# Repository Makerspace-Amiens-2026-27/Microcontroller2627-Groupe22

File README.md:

# Nom du projet

> [!IMPORTANT]
> **À modifier** : ce repo a été créé depuis le template de projet du MakerSpace d'Amiens.
> Remplacez ce README par la présentation de votre projet.
> Les guides d'utilisation du template sont sur le
> [site de documentation du MakerSpace](https://doc.makerspace-amiens.fr/workshops/methodologie-de-projet/).

Une phrase qui explique ce que fait le projet et pour qui.

- **Documentation :** [site du projet](https://makerspace-amiens.github.io/template-project/) (sources dans [`docs/`](docs/))
- **Fichiers du projet :** [`project/`](project/) (CAO, électronique, code)

## Équipe 22

- Maxence DUHAMEL
- Romain DELLIEUX

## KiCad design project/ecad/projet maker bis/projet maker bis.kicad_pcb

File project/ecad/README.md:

# Conception électronique

Un dossier par projet KiCad, contenant au minimum les fichiers `.kicad_pro`,
`.kicad_sch` et `.kicad_pcb`.

| Carte | Dossier | Rôle |
|---|---|---|
| Carte principale, rev A (2 couches) | `projet maker/` | XIAO ESP32S3, écran TFT, joystick, 2 boutons, LED, connecteur I2C |
| Carte principale, rev B (1 couche) | `projet maker bis/` | Même schéma, routage sur une seule face, dessous = plan de masse, 0 via |

Le projet a été fait avec **KiCad 10**. Les bibliothèques ajoutées (XIAO de Seeed Studio,
joystick, bibliothèque du Makerspace) sont dans le dossier `libs/` de chaque projet, donc
le projet s'ouvre directement sans rien installer.

## Affichage sur le site

Pas besoin de recopier les fichiers dans `docs/assets/kicad/` : à chaque push qui
modifie `project/ecad/`, la publication du site copie automatiquement tous les
`.kicad_sch` et `.kicad_pcb` de ce dossier (les espaces des noms deviennent des tirets,
par exemple `projet maker bis.kicad_pcb` devient `projet-maker-bis.kicad_pcb`), puis le
site se met à jour. Le schéma et les deux PCB sont affichés sur la page
**Conception → Électronique → Carte principale**.

## Fichiers à ne pas mettre sur le repo

Les sauvegardes (`*-backups/`), les fichiers de verrou (`*.lck`), `*.kicad_prl` et
les `.bak` sont propres à chaque ordinateur. Ils sont déjà ignorés par `.gitignore`
quand on passe par GitHub Desktop, mais il ne faut pas les glisser à la main sur le
site GitHub.

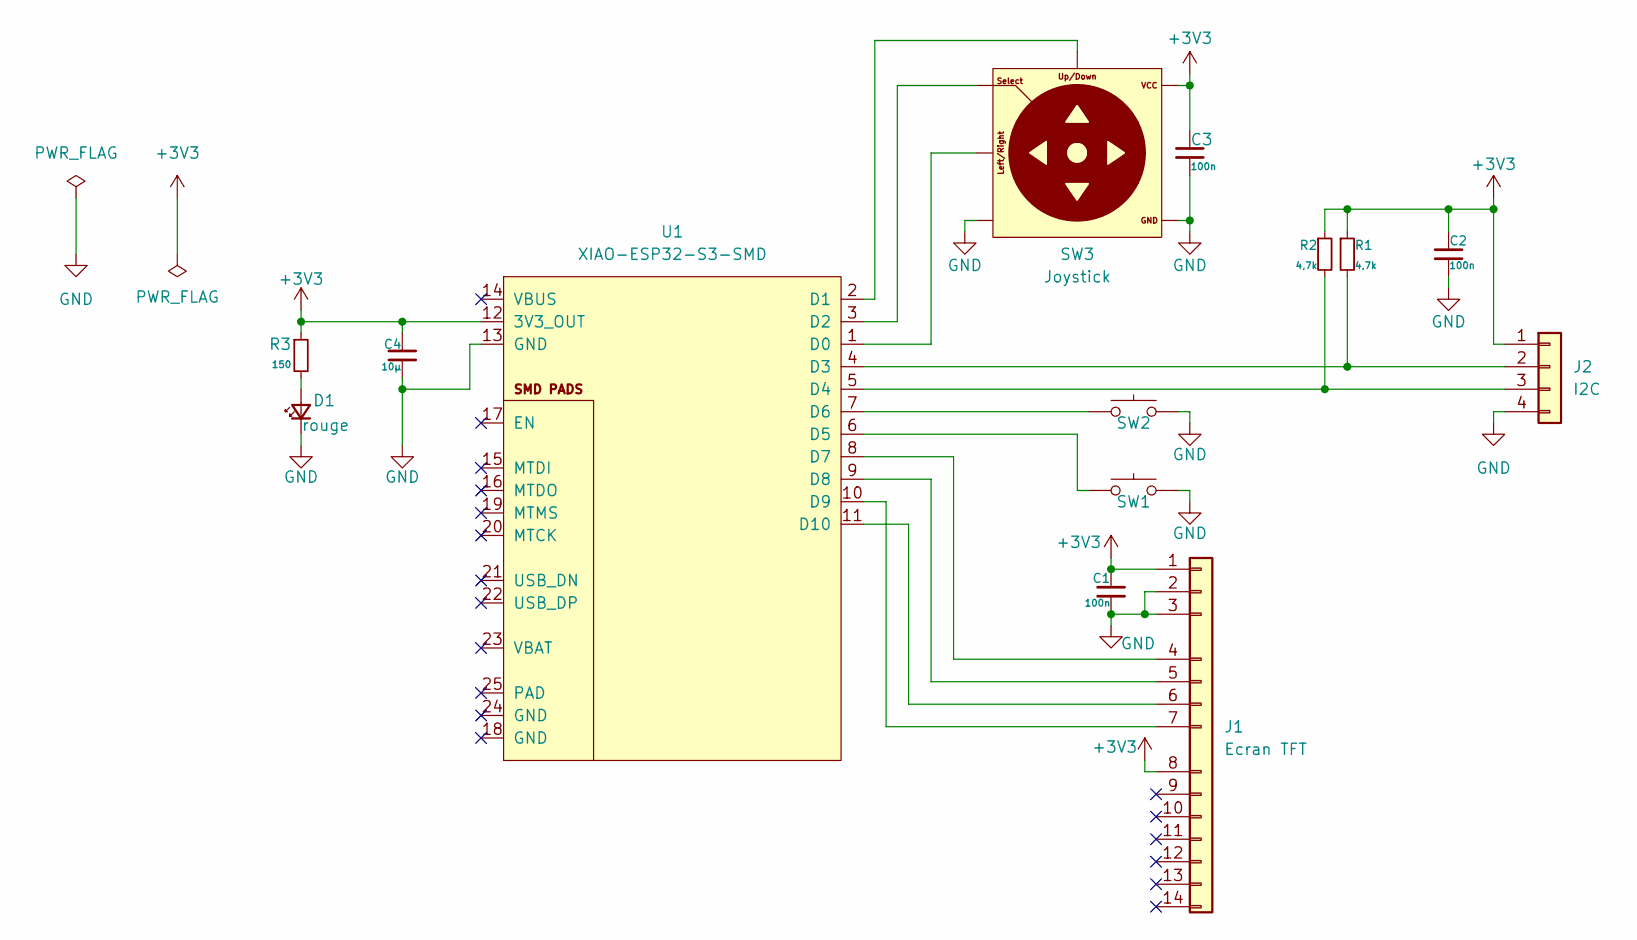
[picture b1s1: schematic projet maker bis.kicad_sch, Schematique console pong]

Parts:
C1, C2, C3: 100n; C_1206
C4: 10µ; C_1206
D1: rouge; LED_1206_3216Metric
J1: Ecran TFT; PinSocket_1x14_P2.54mm_Vertical
J2: I2C; PinHeader_1x04_P2.54mm_Vertical
R1, R2: 4,7k; R_1206
R3: 150; R_1206
SW1: SW1; SW_Push_KMR2
SW2: SW2; SW_Push_KMR2
SW3: Joystick
U1: XIAO-ESP32-S3-SMD; XIAO-ESP32-S3-DIP

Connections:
+3V3: C1.1, C2.1, C3.1, C4.1, J1.1, J1.8, J2.1, R1.1, R2.1, R3.1, SW3.VCC, U1.12 (3V3_OUT)
GND: C1.2, C2.2, C3.2, C4.2, D1.1 (K), J1.2, J1.3, J2.4, SW1.1, SW2.1, SW3.GND, U1.13 (GND)
unnamed: D1.2 (A), R3.2
unnamed: J1.4, U1.8 (D7)
unnamed: J1.5, U1.9 (D8)
unnamed: J1.6, U1.11 (D10)
unnamed: J1.7, U1.10 (D9)
unnamed: J2.2, R1.2, U1.4 (D3)
unnamed: J2.3, R2.2, U1.5 (D4)
unnamed: SW3.Horizontal, U1.1 (D0)
unnamed: SW3.Vertical, U1.2 (D1)
unnamed: SW3.Select, U1.3 (D2)
unnamed: SW1.2, U1.6 (D5)
unnamed: SW2.2, U1.7 (D6)

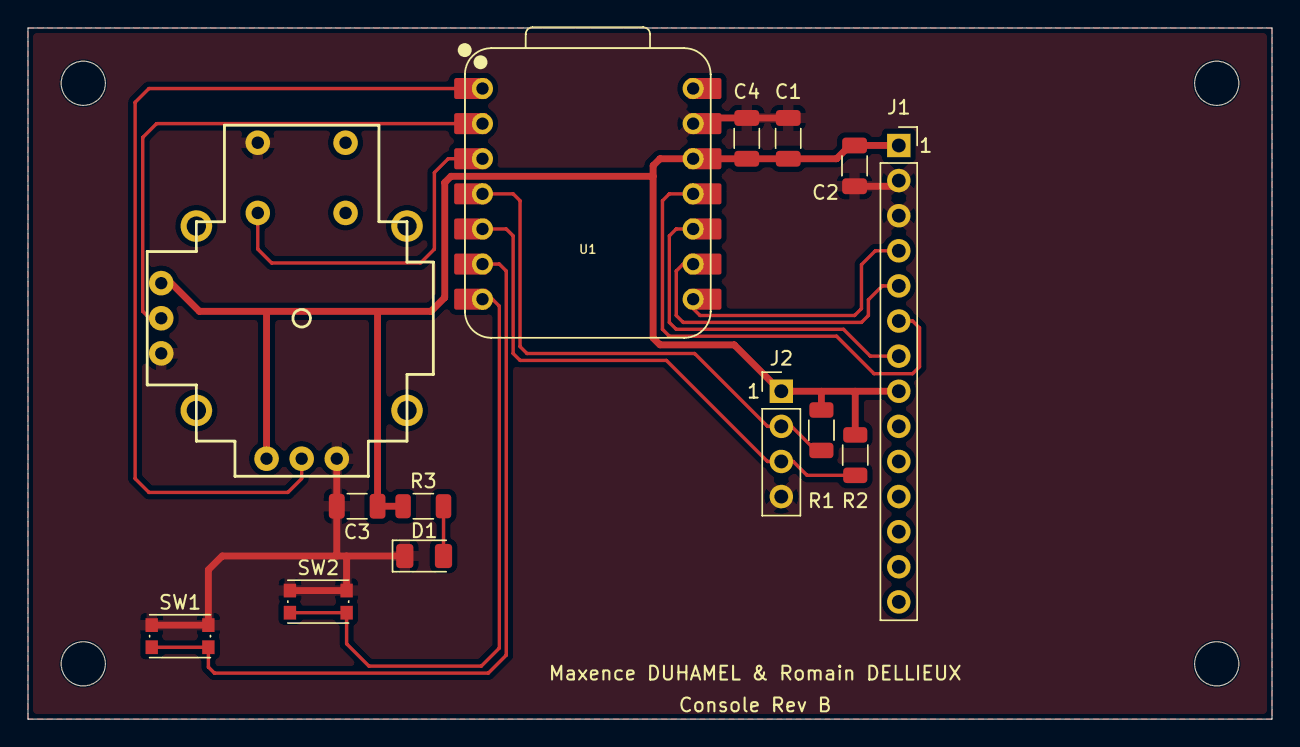
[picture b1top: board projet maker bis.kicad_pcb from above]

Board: 2 copper layers, 90.0 x 50.0 mm, 18 parts (0 on the bottom side), 14 nets.

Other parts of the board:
H1, H2, H3, H4: M3; MountingHole_3.2mm_M3
